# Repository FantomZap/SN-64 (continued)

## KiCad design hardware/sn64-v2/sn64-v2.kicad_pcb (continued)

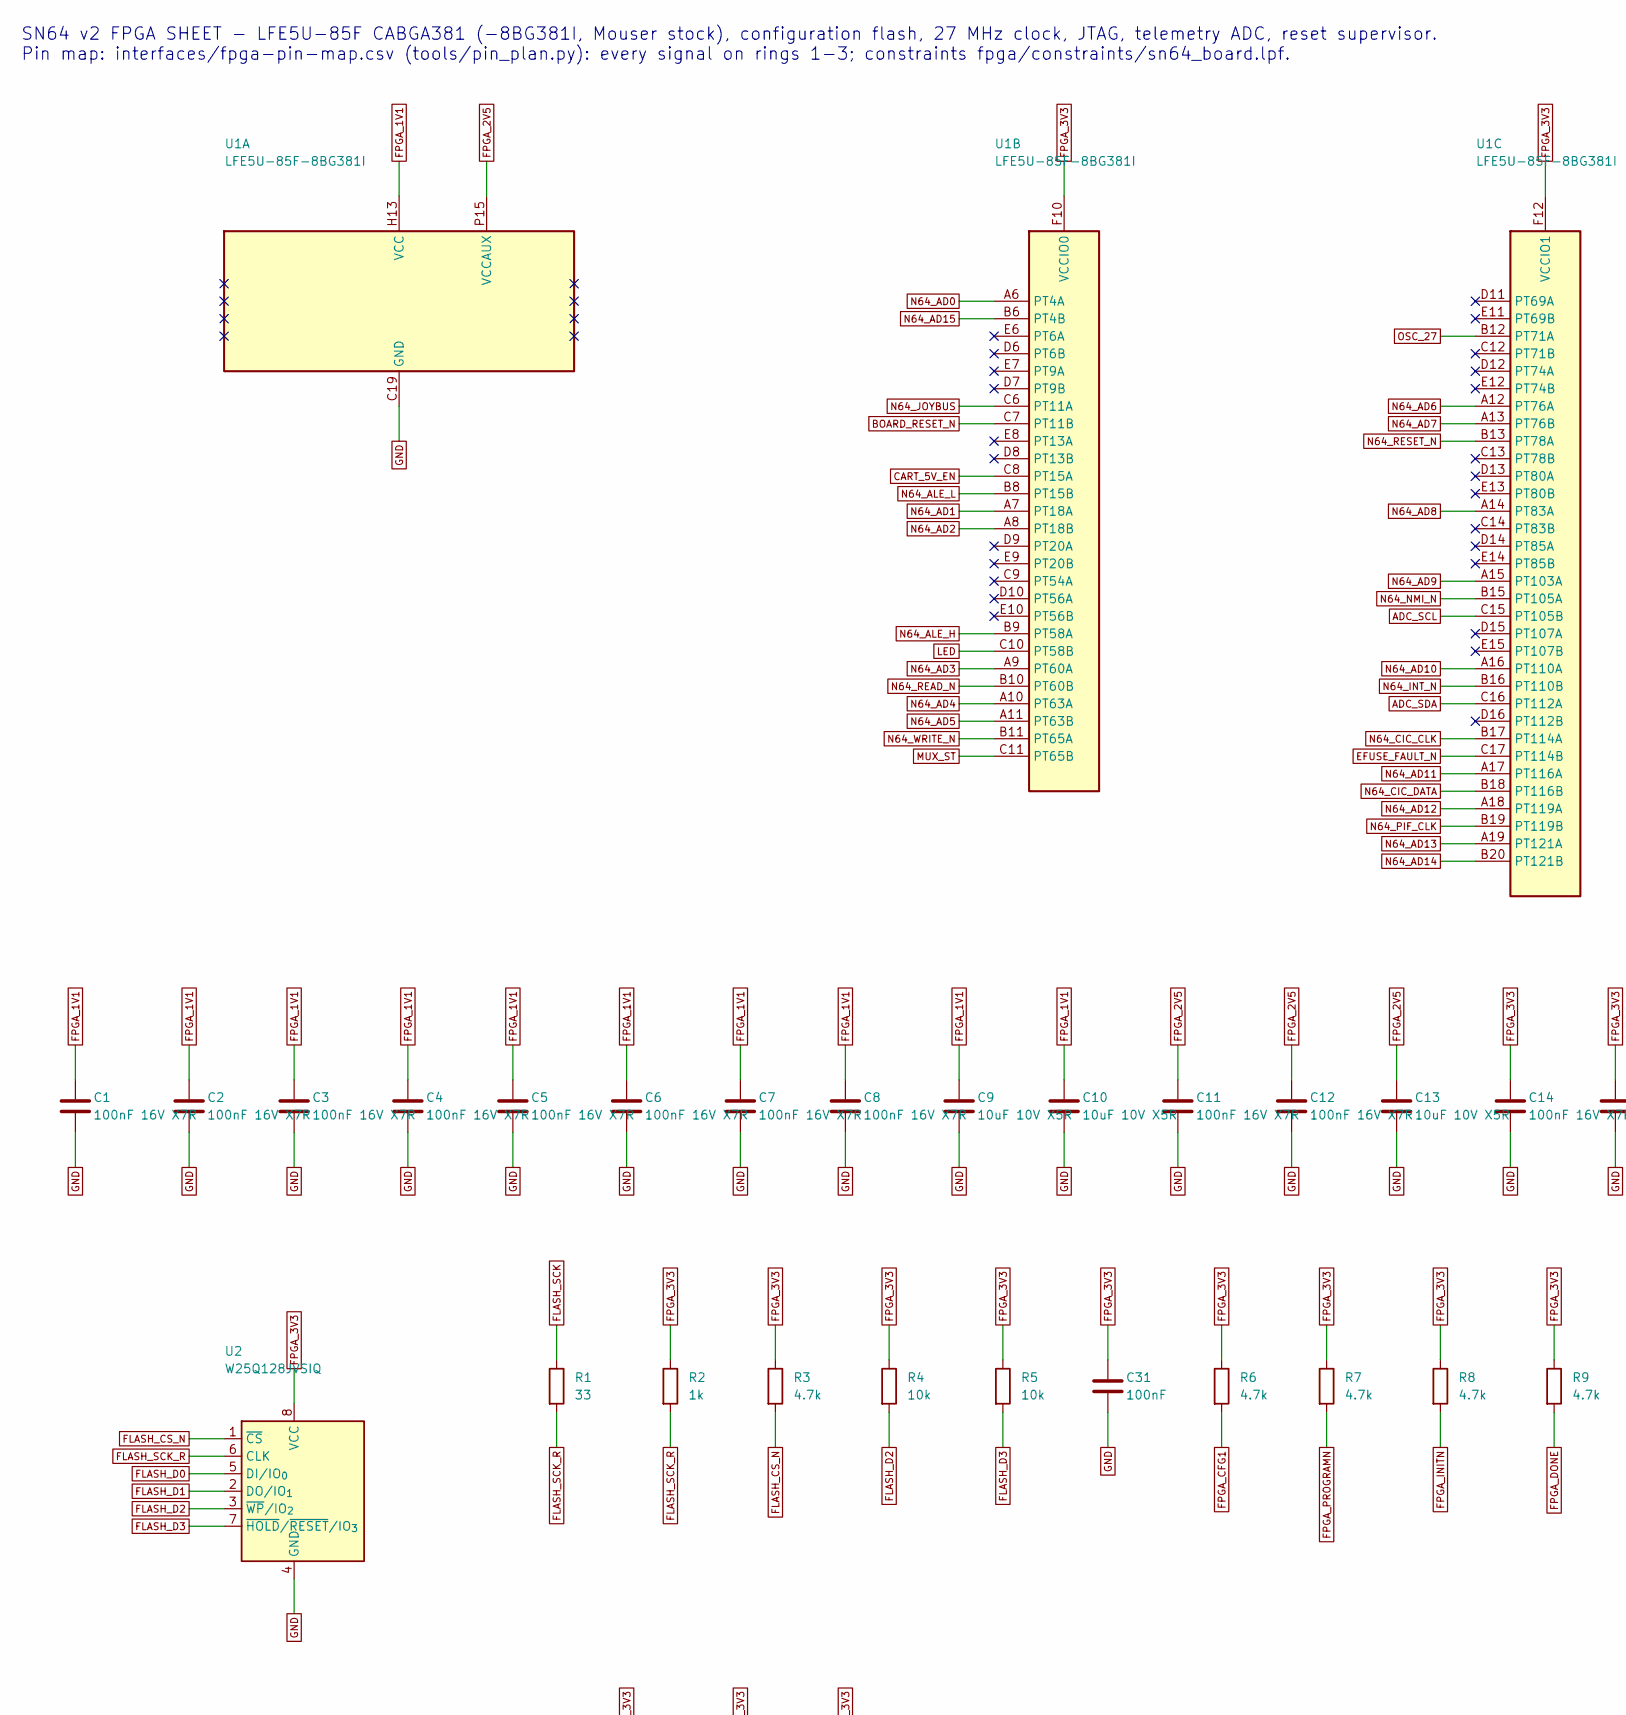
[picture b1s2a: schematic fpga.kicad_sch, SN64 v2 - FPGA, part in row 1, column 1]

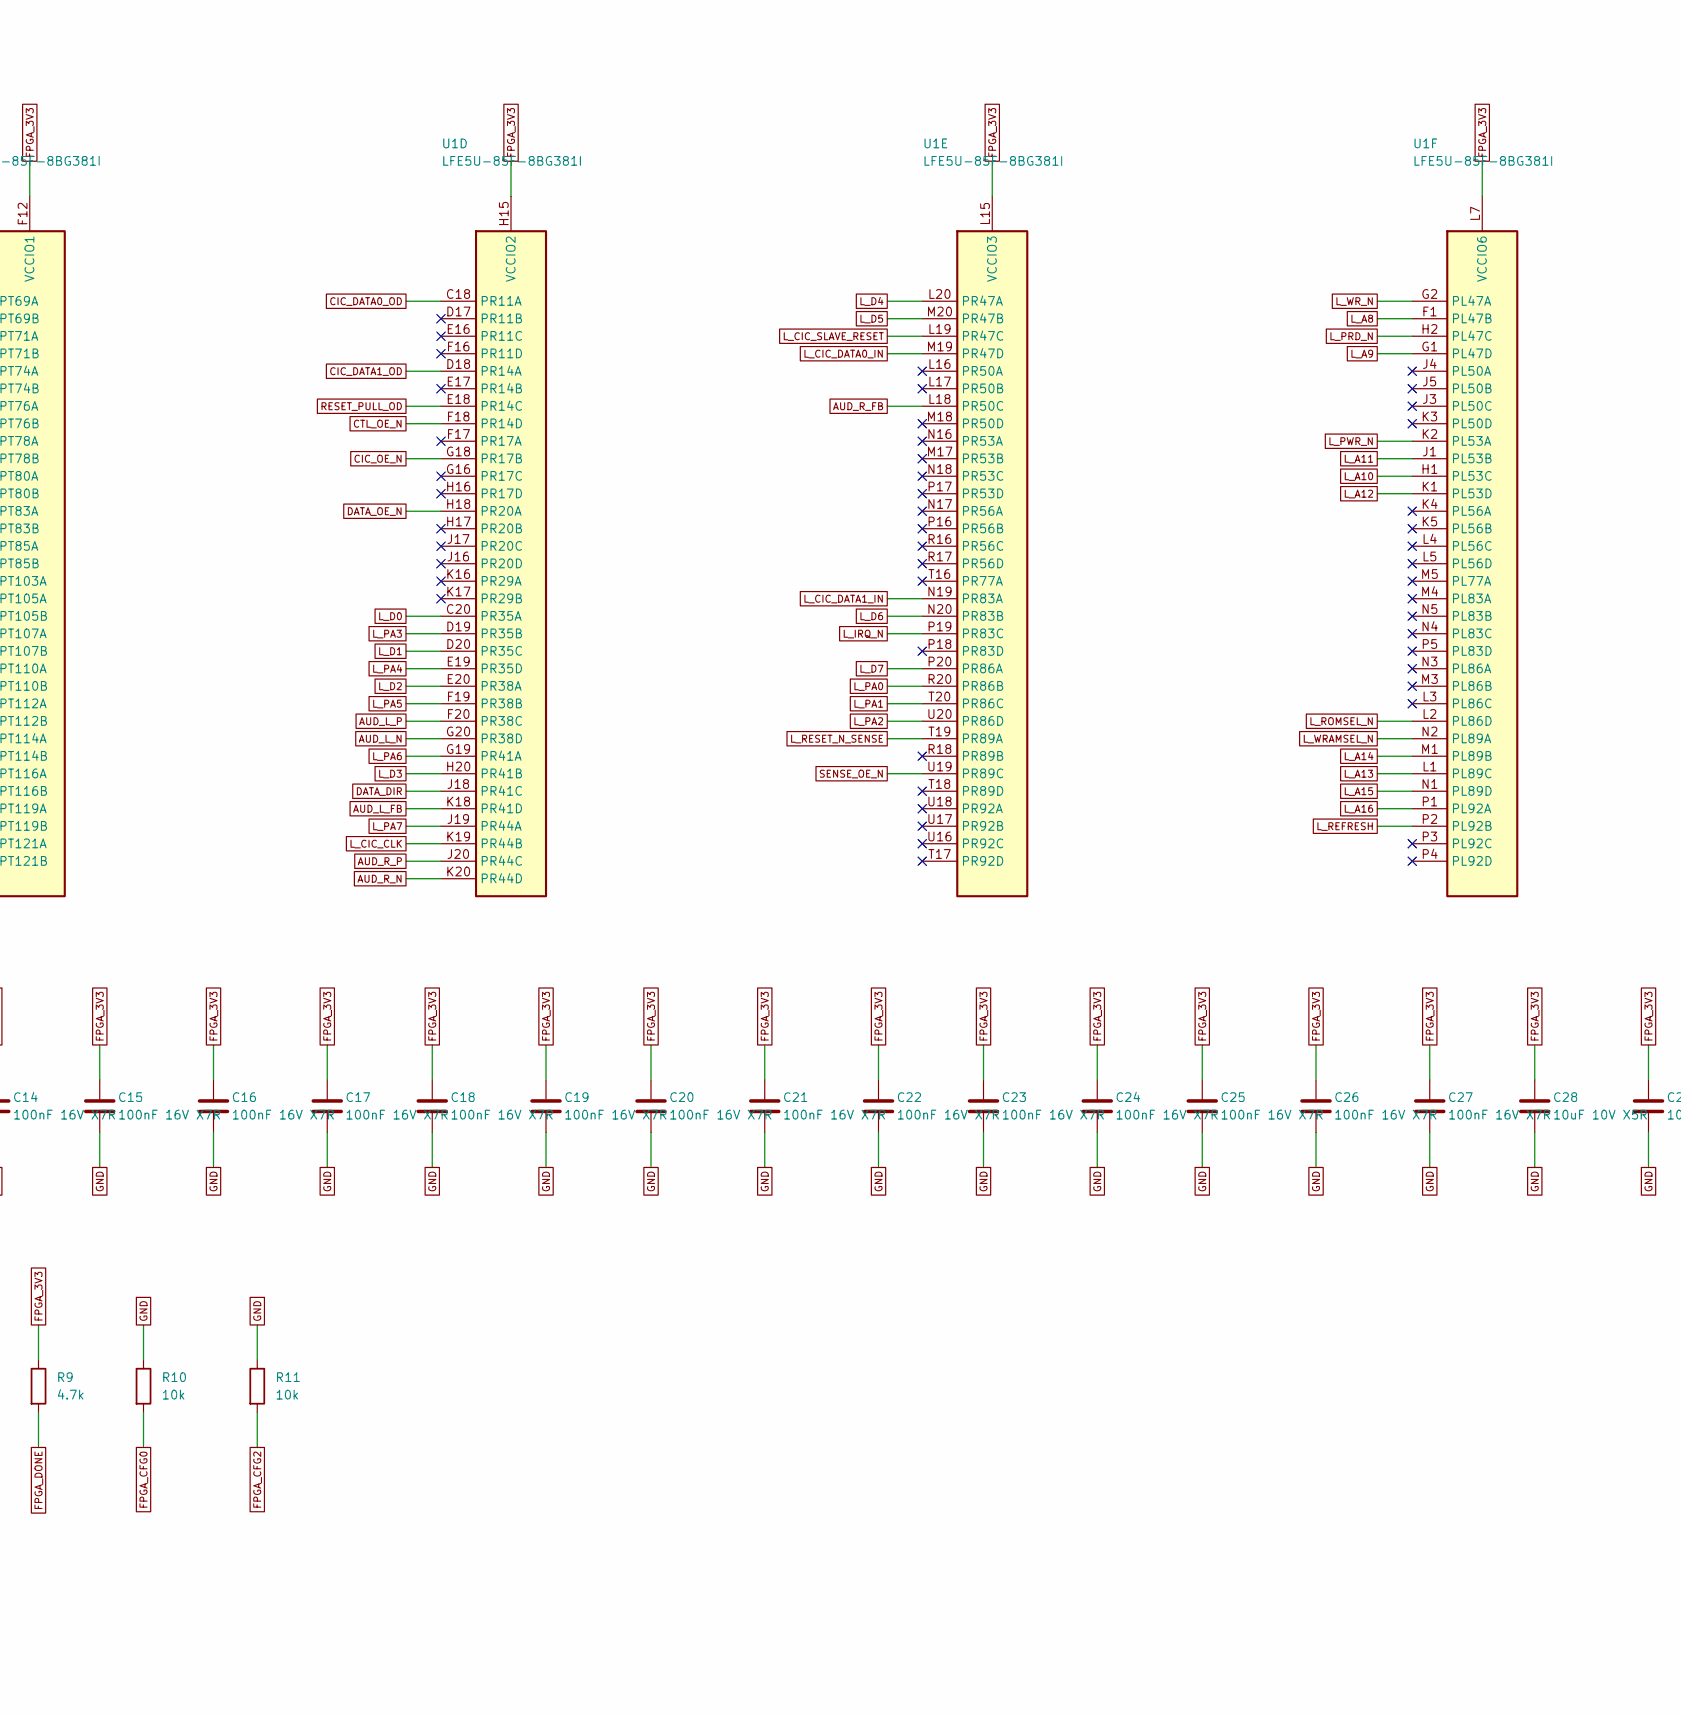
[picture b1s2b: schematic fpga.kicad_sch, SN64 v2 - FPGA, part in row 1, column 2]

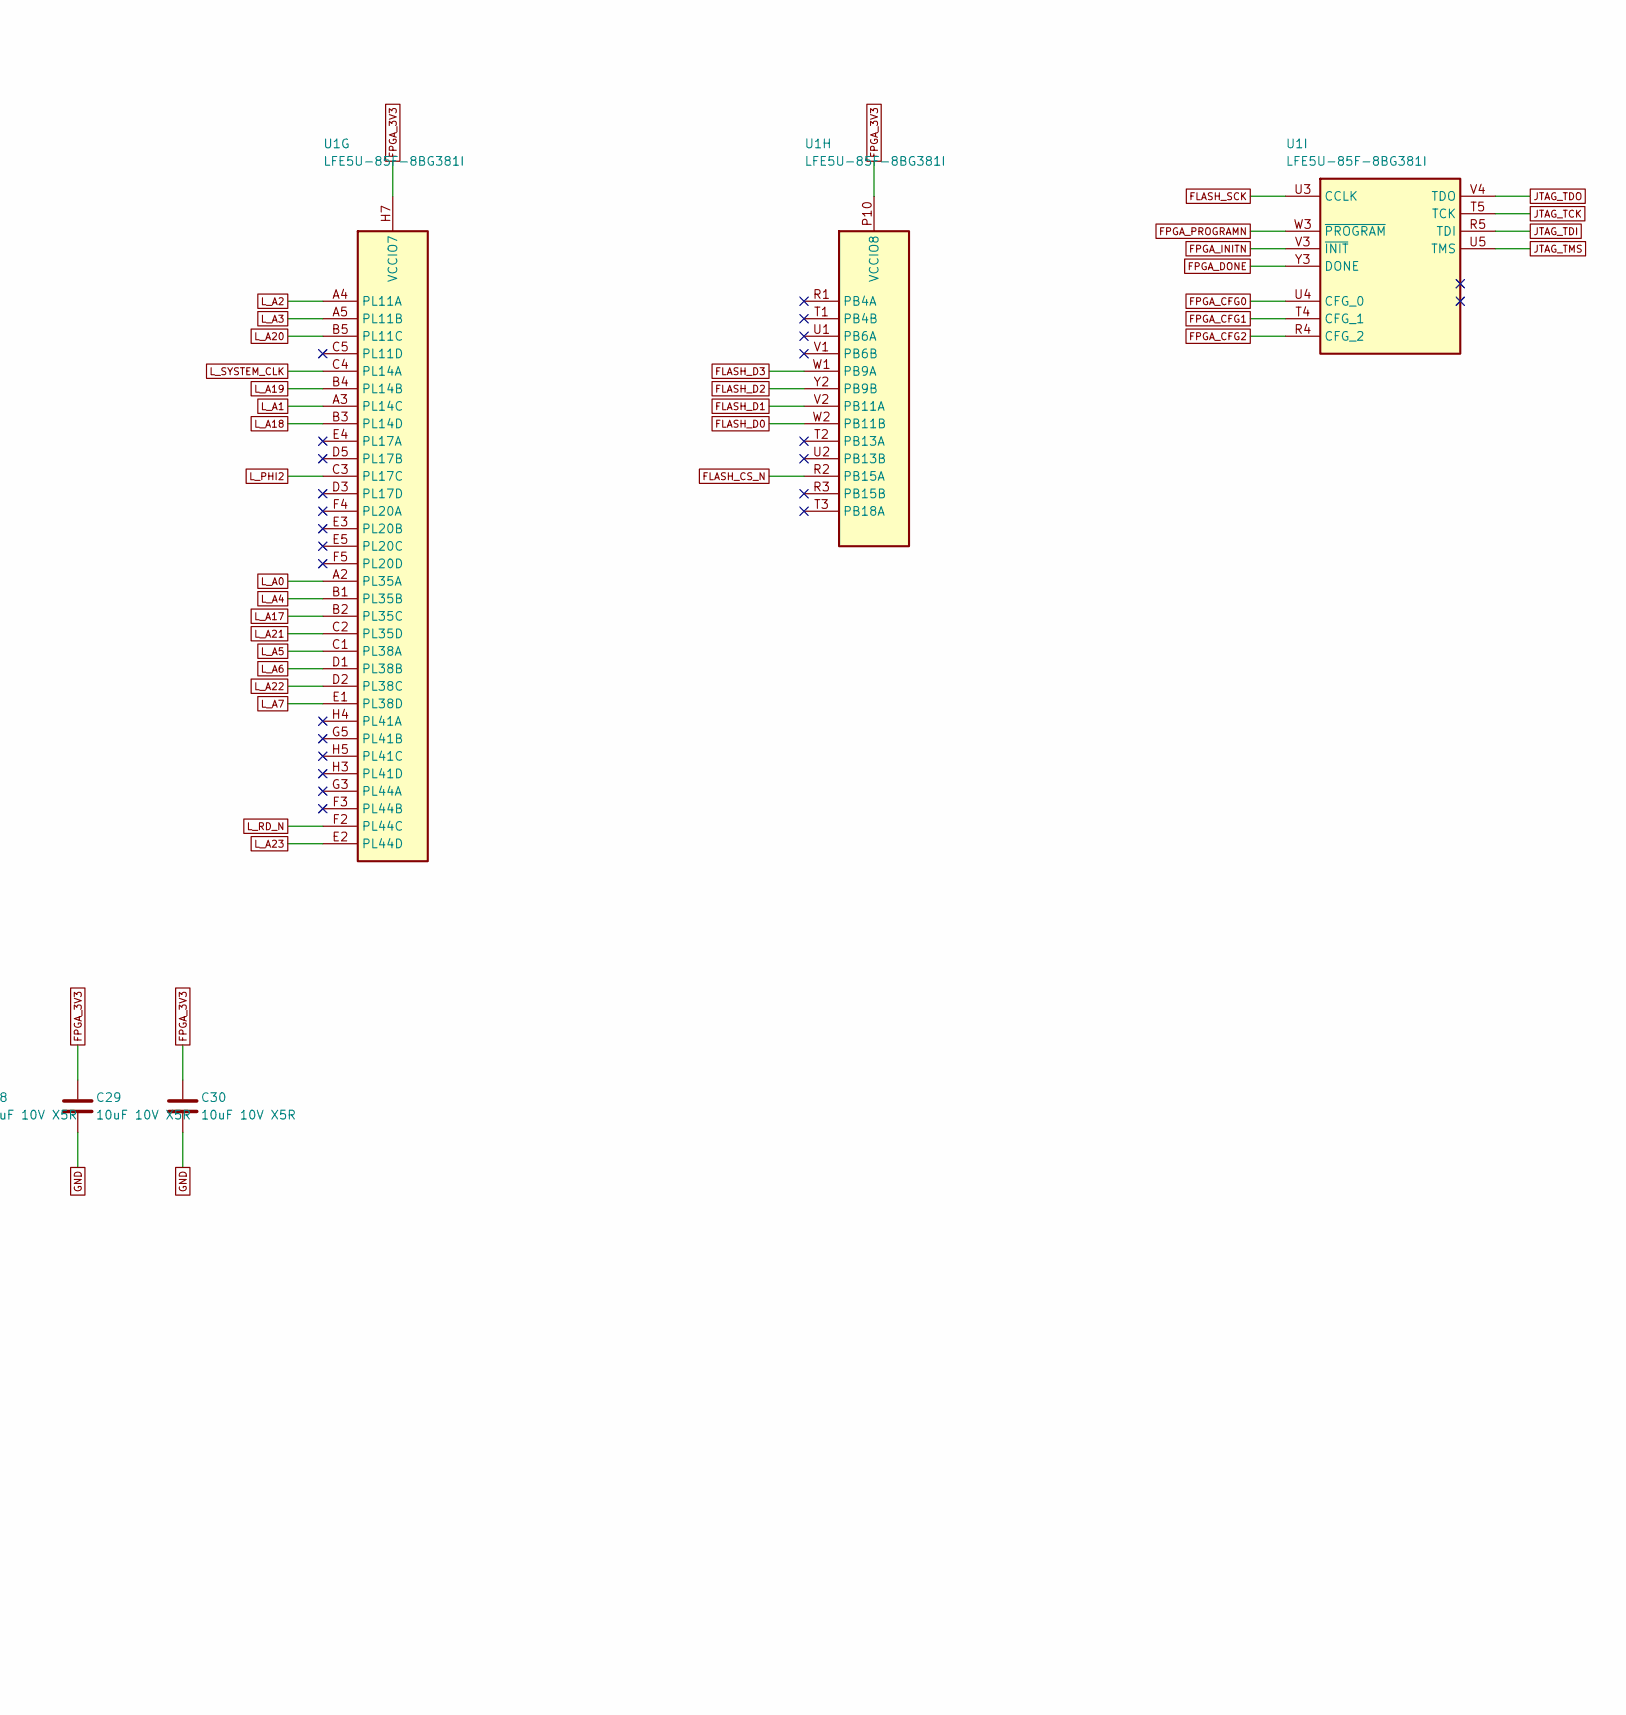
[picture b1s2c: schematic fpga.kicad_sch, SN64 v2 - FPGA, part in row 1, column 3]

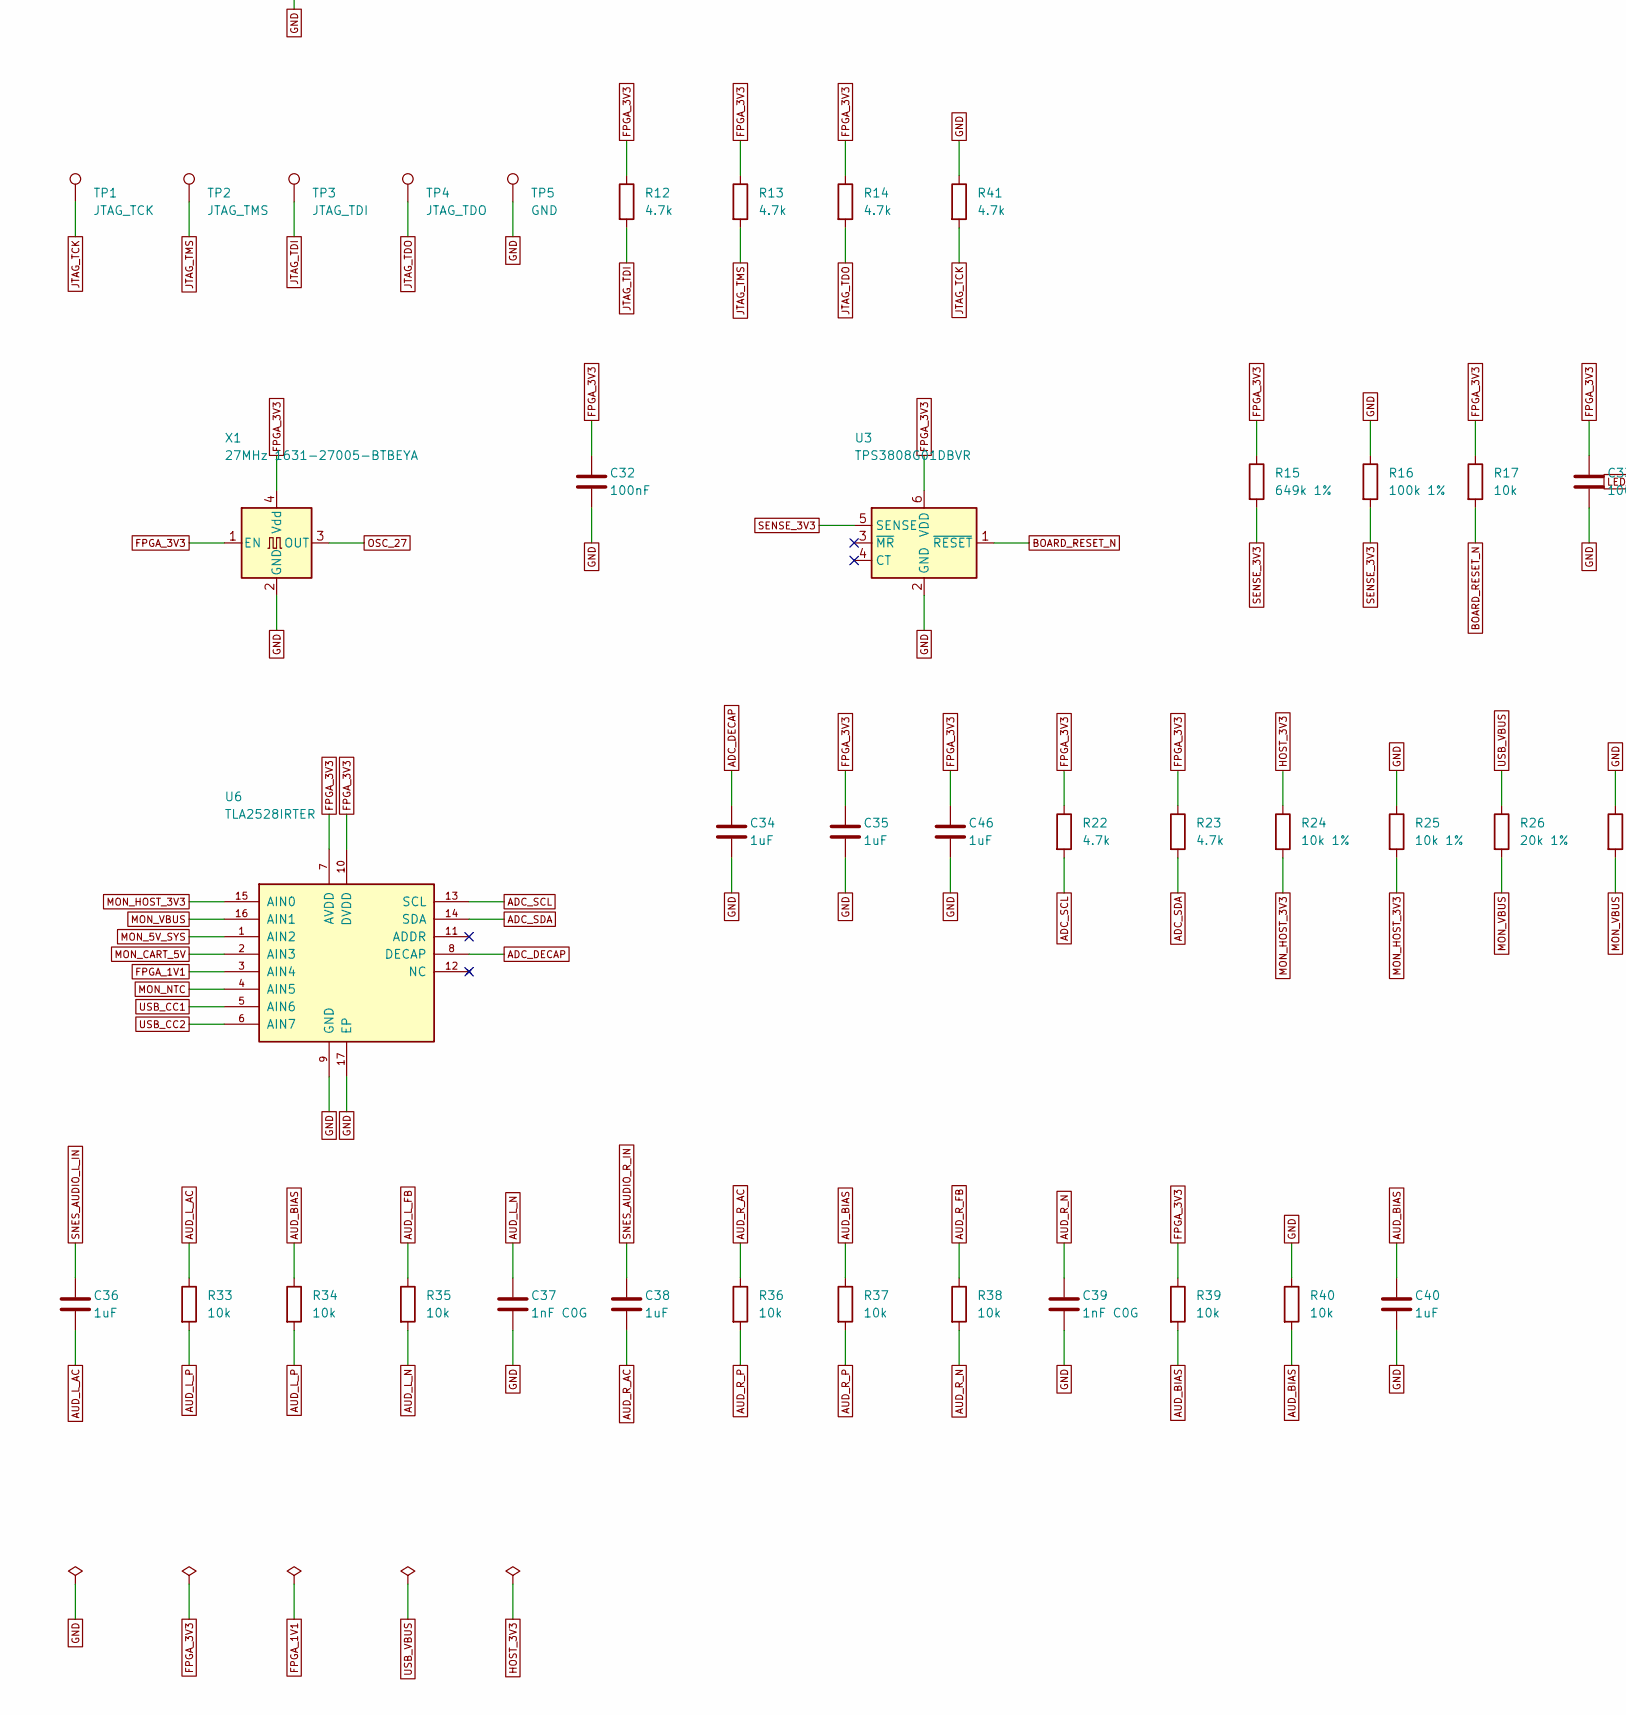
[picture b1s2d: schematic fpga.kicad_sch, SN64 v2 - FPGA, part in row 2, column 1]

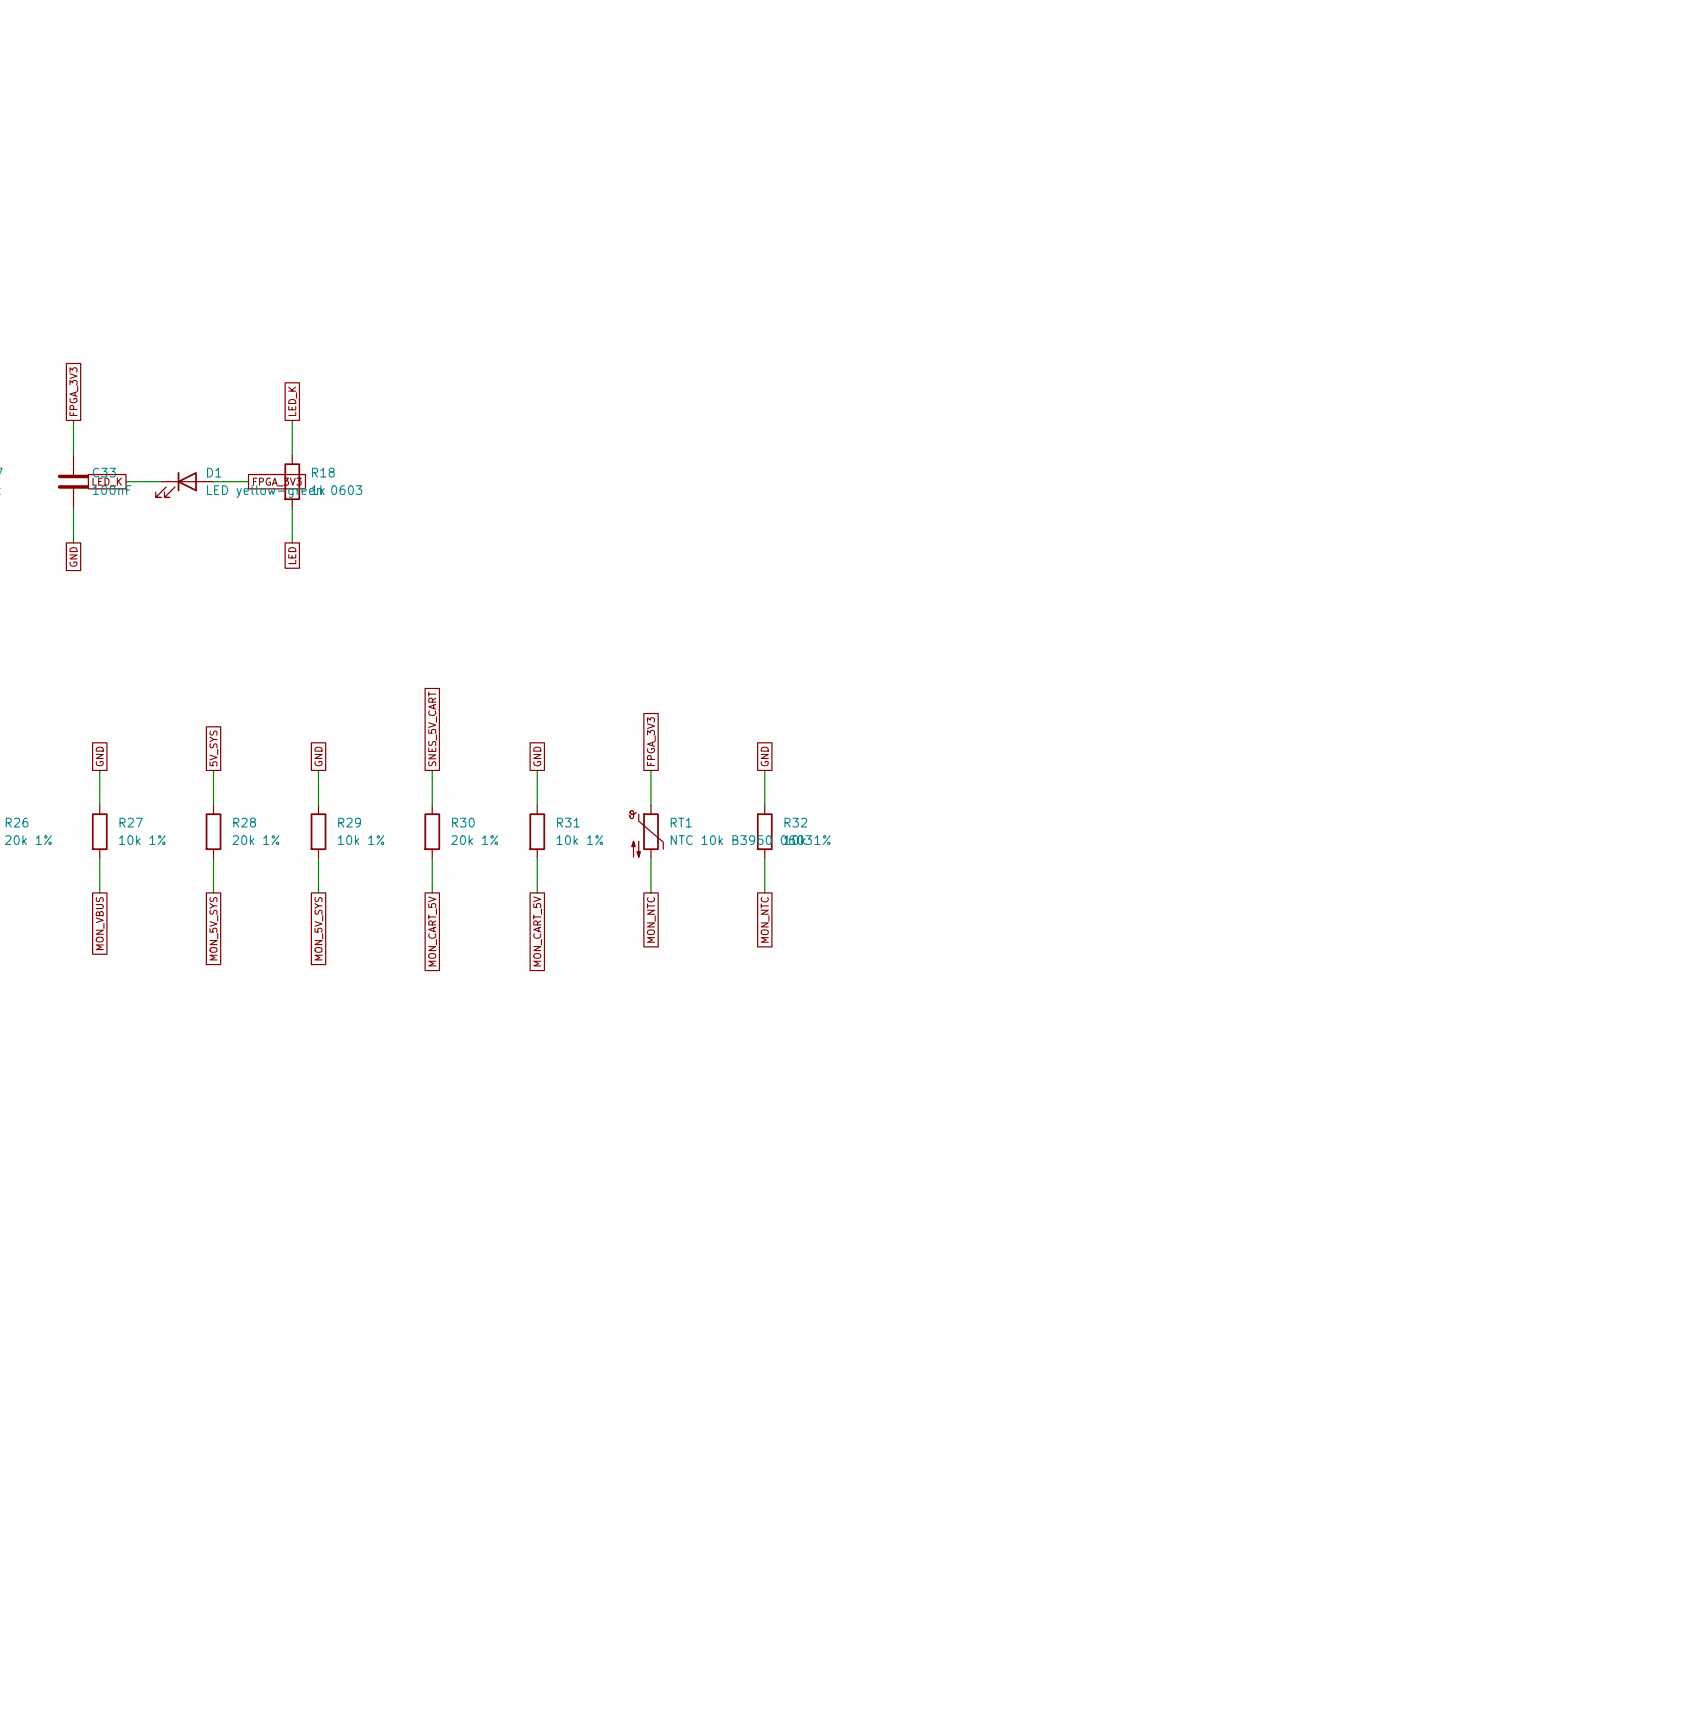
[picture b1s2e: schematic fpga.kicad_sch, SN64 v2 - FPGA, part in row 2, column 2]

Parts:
C1, C2, C3, C4, C5, C6, C7, C8, C11, C12, C14, C15, C16, C17, C18, C19, C20, C21, C22, C23, C24, C25, C26, C27: 100nF 16V X7R; C_0603_1608Metric; MPN CC0603KRX7R9BB104; LCSC C14663
C9, C10, C13, C28, C29, C30: 10uF 10V X5R; C_0805_2012Metric; MPN CL21A106KAYNNNE; LCSC C15850
C31, C32, C33: 100nF; C_0603_1608Metric; MPN CC0603KRX7R9BB104; LCSC C14663
C34, C35, C36, C38, C40, C46: 1uF; C_0603_1608Metric; MPN CL10A105KB8NNNC; LCSC C15849
C37, C39: 1nF C0G; C_0603_1608Metric; MPN CL10C102JB8NNNC; LCSC C163508
D1: LED yellow-green 0603; LED_0603_1608Metric; MPN 19-21SYGC/S530-E2/4T; LCSC C2986011
R1: 33; R_0603_1608Metric; MPN 0603WAF330JT5E; LCSC C23140
R2, R18: 1k; R_0603_1608Metric; MPN 0603WAF1001T5E; LCSC C21190
R3, R6, R7, R8, R9, R12, R13, R14, R22, R23, R41: 4.7k; R_0603_1608Metric; MPN 0603WAF4701T5E; LCSC C23162
R4, R5, R10, R11, R17, R33, R34, R35, R36, R37, R38, R39, R40: 10k; R_0603_1608Metric; MPN 0603WAF1002T5E; LCSC C25804
R15: 649k 1%; R_0603_1608Metric; MPN FRC0603F6493TS; LCSC C2999594
R16: 100k 1%; R_0603_1608Metric; MPN 0603WAF1003T5E; LCSC C25803
R24, R25, R27, R29, R31, R32: 10k 1%; R_0603_1608Metric; MPN 0603WAF1002T5E; LCSC C25804
R26, R28, R30: 20k 1%; R_0603_1608Metric; MPN 0603WAF2002T5E; LCSC C4184
RT1: NTC 10k B3950 0603; R_0603_1608Metric; MPN SDNT1608X103F3950FTF; LCSC C279936
TP1: JTAG_TCK; TestPoint_Pad_1.5x1.5mm
TP2: JTAG_TMS; TestPoint_Pad_1.5x1.5mm
TP3: JTAG_TDI; TestPoint_Pad_1.5x1.5mm
TP4: JTAG_TDO; TestPoint_Pad_1.5x1.5mm
TP5: GND; TestPoint_Pad_1.5x1.5mm
U1: LFE5U-85F-8BG381I; Lattice_caBGA-381_17x17mm_Layout20x20_P0.8mm; MPN LFE5U-85F-8BG381I
U2: W25Q128JVSIQ; SOIC-8_5.3x5.3mm_P1.27mm; MPN W25Q128JVSIQ; LCSC C97521
U3: TPS3808G01DBVR; SOT-23-6; MPN TPS3808G01DBVR; LCSC C19653
U6: TLA2528IRTER; WQFN-16-1EP_3x3mm_P0.5mm_EP1.68x1.68mm; MPN TLA2528IRTER; LCSC C2866175
X1: 27MHz 1631-27005-BTBEYA; Oscillator_SMD_Abracon_ASE-4Pin_3.2x2.5mm; MPN 1631-27005-BTBEYA; LCSC C3003262

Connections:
5V_SYS: R28.1; also elsewhere on the board
ADC_DECAP: C34.1, U6.8 (DECAP)
ADC_SCL: R22.2, U1.C15 (PT105B), U6.13 (SCL)
ADC_SDA: R23.2, U1.C16 (PT112A), U6.14 (SDA)
AUD_BIAS: C40.1, R34.1, R37.1, R39.2, R40.2
AUD_L_AC: C36.2, R33.1
AUD_L_FB: R35.1, U1.K18 (PR41D)
AUD_L_N: C37.1, R35.2, U1.G20 (PR38D)
AUD_L_P: R33.2, R34.2, U1.F20 (PR38C)
AUD_R_AC: C38.2, R36.1
AUD_R_FB: R38.1, U1.L18 (PR50C)
AUD_R_N: C39.1, R38.2, U1.K20 (PR44D)
AUD_R_P: R36.2, R37.2, U1.J20 (PR44C)
BOARD_RESET_N: R17.2, U1.C7 (PT11B), U3.1 (~RESET)
CART_5V_EN: U1.C8 (PT15A); also elsewhere on the board
CIC_DATA0_OD: U1.C18 (PR11A); also elsewhere on the board
CIC_DATA1_OD: U1.D18 (PR14A); also elsewhere on the board
CIC_OE_N: U1.G18 (PR17B); also elsewhere on the board
CTL_OE_N: U1.F18 (PR14D); also elsewhere on the board
DATA_DIR: U1.J18 (PR41C); also elsewhere on the board
DATA_OE_N: U1.H18 (PR20A); also elsewhere on the board
EFUSE_FAULT_N: U1.C17 (PT114B); also elsewhere on the board
FLASH_CS_N: R3.2, U1.R2 (PB15A), U2.1 (~CS)
FLASH_D0: U1.W2 (PB11B), U2.5 (DI/IO_{0})
FLASH_D1: U1.V2 (PB11A), U2.2 (DO/IO_{1})
FLASH_D2: R4.2, U1.Y2 (PB9B), U2.3 (~WP/IO_{2})
FLASH_D3: R5.2, U1.W1 (PB9A), U2.7 (~HOLD/~RESET/IO_{3})
FLASH_SCK: R1.1, U1.U3 (CCLK)
FLASH_SCK_R: R1.2, R2.2, U2.6 (CLK)
FPGA_1V1: C1.1, C2.1, C3.1, C4.1, C5.1, C6.1, C7.1, C8.1, C9.1, C10.1, U1.H8 (VCC), U1.H9 (VCC), U1.H10 (VCC), U1.H11 (VCC), U1.H12 (VCC), U1.H13 (VCC), U1.J8 (VCC), U1.J13 (VCC), U1.K8 (VCC), U1.K13 (VCC), U1.L8 (VCC), U1.L13 (VCC), U1.M8 (VCC), U1.M13 (VCC), U1.N8 (VCC), U1.N9 (VCC), U1.N10 (VCC), U1.N11 (VCC), U1.N12 (VCC), U1.N13 (VCC), U6.3 (AIN4); also elsewhere on the board
FPGA_2V5: C11.1, C12.1, C13.1, U1.F6 (VCCAUX), U1.F15 (VCCAUX), U1.P6 (VCCAUX), U1.P15 (VCCAUX); also elsewhere on the board
FPGA_3V3: C14.1, C15.1, C16.1, C17.1, C18.1, C19.1, C20.1, C21.1, C22.1, C23.1, C24.1, C25.1, C26.1, C27.1, C28.1, C29.1, C30.1, C31.1, C32.1, C33.1, C35.1, C46.1, D1.2 (A), R2.1, R3.1, R4.1, R5.1, R6.1, R7.1, R8.1, R9.1, R12.1, R13.1, R14.1, R15.1, R17.1, R22.1, R23.1, R39.1, RT1.1, U1.F9 (VCCIO0), U1.F10 (VCCIO0), U1.F11 (VCCIO1), U1.F12 (VCCIO1), U1.H6 (VCCIO7), U1.H7 (VCCIO7), U1.H14 (VCCIO2), U1.H15 (VCCIO2), U1.J6 (VCCIO7), U1.J15 (VCCIO2), U1.L6 (VCCIO6), U1.L7 (VCCIO6), U1.L14 (VCCIO3), U1.L15 (VCCIO3), U1.M6 (VCCIO6), U1.M15 (VCCIO3), U1.P9 (VCCIO8), U1.P10 (VCCIO8), U2.8 (VCC), U3.6 (VDD), U6.7 (AVDD), U6.10 (DVDD), X1.1 (EN), X1.4 (Vdd); also elsewhere on the board
FPGA_CFG0: R10.2, U1.U4 (CFG_0)
FPGA_CFG1: R6.2, U1.T4 (CFG_1)
FPGA_CFG2: R11.2, U1.R4 (CFG_2)
FPGA_DONE: R9.2, U1.Y3 (DONE)
FPGA_INITN: R8.2, U1.V3 (~INIT)
FPGA_PROGRAMN: R7.2, U1.W3 (~PROGRAM)
GND: C1.2, C2.2, C3.2, C4.2, C5.2, C6.2, C7.2, C8.2, C9.2, C10.2, C11.2, C12.2, C13.2, C14.2, C15.2, C16.2, C17.2, C18.2, C19.2, C20.2, C21.2, C22.2, C23.2, C24.2, C25.2, C26.2, C27.2, C28.2, C29.2, C30.2, C31.2, C32.2, C33.2, C34.2, C35.2, C37.2, C39.2, C40.2, C46.2, R10.1, R11.1, R16.1, R25.1, R27.1, R29.1, R31.1, R32.1, R40.1, R41.1, TP5.1, U1.B7 (GND), U1.B14 (GND), U1.C19 (GND), U1.D4 (GND), U1.F7 (GND), U1.F8 (GND), U1.F13 (GND), U1.F14 (GND), U1.G4 (GND), U1.G6 (GND), U1.G7 (GND), U1.G8 (GND), U1.G9 (GND), U1.G10 (GND), U1.G11 (GND), U1.G12 (GND), U1.G13 (GND), U1.G14 (GND), U1.G15 (GND), U1.G17 (GND), U1.H19 (GND), U1.J2 (GND), U1.J7 (GND), U1.J9 (GND), U1.J10 (GND), U1.J11 (GND), U1.J12 (GND), U1.J14 (GND), U1.K6 (GND), U1.K7 (GND), U1.K9 (GND), U1.K10 (GND), U1.K11 (GND), U1.K12 (GND), U1.K14 (GND), U1.K15 (GND), U1.L9 (GND), U1.L10 (GND), U1.L11 (GND), U1.L12 (GND), U1.M2 (GND), U1.M7 (GND), U1.M9 (GND), U1.M10 (GND), U1.M11 (GND), U1.M12 (GND), U1.M14 (GND), U1.M16 (GND), U1.N6 (GND), U1.N7 (GND), U1.N14 (GND), U1.N15 (GND), U1.P7 (GND), U1.P8 (GND), U1.P11 (GND), U1.P12 (GND), U1.P13 (GND), U1.P14 (GND), U1.R19 (GND), U1.T6 (GND), U1.T7 (GND), U1.T8 (GND), U1.T9 (GND), U1.T10 (GND), U1.T11 (GND), U1.T12 (GND), U1.T13 (GND), U1.T14 (GND), U1.T15 (GND), U1.U6 (GND), U1.U7 (GND), U1.U8 (GND), U1.U9 (GND), U1.U10 (GND), U1.U11 (GND), U1.U12 (GND), U1.U13 (GND), U1.U14 (GND), U1.U15 (GND), U1.V5 (GND), U1.V6 (GND), U1.V7 (GND), U1.V8 (GND), U1.V9 (GND), U1.V10 (GND), U1.V11 (GND), U1.V12 (GND), U1.V13 (GND), U1.V14 (GND), U1.V15 (GND), U1.V16 (GND), U1.V17 (GND), U1.V18 (GND), U1.V19 (GND), U1.V20 (GND), U1.W6 (GND), U1.W7 (GND), U1.W12 (GND), U1.W15 (GND), U1.W16 (GND), U1.W19 (GND), U1.W20 (GND), U1.Y5 (GND), U1.Y6 (GND), U1.Y7 (GND), U1.Y8 (GND), U1.Y11 (GND), U1.Y12 (GND), U1.Y14 (GND), U1.Y15 (GND), U1.Y16 (GND), U1.Y17 (GND), U1.Y19 (GND), U2.4 (GND), U3.2 (GND), U6.9 (GND), U6.17 (EP), X1.2 (GND); also elsewhere on the board
HOST_3V3: R24.1; also elsewhere on the board
JTAG_TCK: R41.2, TP1.1, U1.T5 (TCK); also elsewhere on the board
JTAG_TDI: R12.2, TP3.1, U1.R5 (TDI); also elsewhere on the board
JTAG_TDO: R14.2, TP4.1, U1.V4 (TDO); also elsewhere on the board
JTAG_TMS: R13.2, TP2.1, U1.U5 (TMS); also elsewhere on the board
LED: R18.2, U1.C10 (PT58B)
LED_K: D1.1 (K), R18.1
L_A0: U1.A2 (PL35A); also elsewhere on the board
L_A1: U1.A3 (PL14C); also elsewhere on the board
L_A2: U1.A4 (PL11A); also elsewhere on the board
L_A3: U1.A5 (PL11B); also elsewhere on the board
L_A4: U1.B1 (PL35B); also elsewhere on the board
L_A5: U1.C1 (PL38A); also elsewhere on the board
L_A6: U1.D1 (PL38B); also elsewhere on the board
L_A7: U1.E1 (PL38D); also elsewhere on the board
L_A8: U1.F1 (PL47B); also elsewhere on the board
L_A9: U1.G1 (PL47D); also elsewhere on the board
L_A10: U1.H1 (PL53C); also elsewhere on the board
L_A11: U1.J1 (PL53B); also elsewhere on the board
L_A12: U1.K1 (PL53D); also elsewhere on the board
L_A13: U1.L1 (PL89C); also elsewhere on the board
L_A14: U1.M1 (PL89B); also elsewhere on the board
L_A15: U1.N1 (PL89D); also elsewhere on the board
L_A16: U1.P1 (PL92A); also elsewhere on the board
L_A17: U1.B2 (PL35C); also elsewhere on the board
L_A18: U1.B3 (PL14D); also elsewhere on the board
L_A19: U1.B4 (PL14B); also elsewhere on the board
L_A20: U1.B5 (PL11C); also elsewhere on the board
L_A21: U1.C2 (PL35D); also elsewhere on the board
L_A22: U1.D2 (PL38C); also elsewhere on the board
L_A23: U1.E2 (PL44D); also elsewhere on the board
L_CIC_CLK: U1.K19 (PR44B); also elsewhere on the board
L_CIC_DATA0_IN: U1.M19 (PR47D); also elsewhere on the board
L_CIC_DATA1_IN: U1.N19 (PR83A); also elsewhere on the board
L_CIC_SLAVE_RESET: U1.L19 (PR47C); also elsewhere on the board
L_D0: U1.C20 (PR35A); also elsewhere on the board
L_D1: U1.D20 (PR35C); also elsewhere on the board
L_D2: U1.E20 (PR38A); also elsewhere on the board
L_D3: U1.H20 (PR41B); also elsewhere on the board
L_D4: U1.L20 (PR47A); also elsewhere on the board
L_D5: U1.M20 (PR47B); also elsewhere on the board
L_D6: U1.N20 (PR83B); also elsewhere on the board
L_D7: U1.P20 (PR86A); also elsewhere on the board
L_IRQ_N: U1.P19 (PR83C); also elsewhere on the board
L_PA0: U1.R20 (PR86B); also elsewhere on the board
L_PA1: U1.T20 (PR86C); also elsewhere on the board
L_PA2: U1.U20 (PR86D); also elsewhere on the board
L_PA3: U1.D19 (PR35B); also elsewhere on the board
L_PA4: U1.E19 (PR35D); also elsewhere on the board
L_PA5: U1.F19 (PR38B); also elsewhere on the board
L_PA6: U1.G19 (PR41A); also elsewhere on the board
L_PA7: U1.J19 (PR44A); also elsewhere on the board
L_PHI2: U1.C3 (PL17C); also elsewhere on the board
L_PRD_N: U1.H2 (PL47C); also elsewhere on the board
L_PWR_N: U1.K2 (PL53A); also elsewhere on the board
L_RD_N: U1.F2 (PL44C); also elsewhere on the board
L_REFRESH: U1.P2 (PL92B); also elsewhere on the board
L_RESET_N_SENSE: U1.T19 (PR89A); also elsewhere on the board
L_ROMSEL_N: U1.L2 (PL86D); also elsewhere on the board
L_SYSTEM_CLK: U1.C4 (PL14A); also elsewhere on the board
L_WRAMSEL_N: U1.N2 (PL89A); also elsewhere on the board
L_WR_N: U1.G2 (PL47A); also elsewhere on the board
MON_5V_SYS: R28.2, R29.2, U6.1 (AIN2)
MON_CART_5V: R30.2, R31.2, U6.2 (AIN3)
MON_HOST_3V3: R24.2, R25.2, U6.15 (AIN0)
MON_NTC: R32.2, RT1.2, U6.4 (AIN5)
MON_VBUS: R26.2, R27.2, U6.16 (AIN1)
MUX_ST: U1.C11 (PT65B); also elsewhere on the board
N64_AD0: U1.A6 (PT4A); also elsewhere on the board
N64_AD1: U1.A7 (PT18A); also elsewhere on the board
N64_AD2: U1.A8 (PT18B); also elsewhere on the board
N64_AD3: U1.A9 (PT60A); also elsewhere on the board
N64_AD4: U1.A10 (PT63A); also elsewhere on the board
N64_AD5: U1.A11 (PT63B); also elsewhere on the board
N64_AD6: U1.A12 (PT76A); also elsewhere on the board
N64_AD7: U1.A13 (PT76B); also elsewhere on the board
N64_AD8: U1.A14 (PT83A); also elsewhere on the board
N64_AD9: U1.A15 (PT103A); also elsewhere on the board
N64_AD10: U1.A16 (PT110A); also elsewhere on the board
N64_AD11: U1.A17 (PT116A); also elsewhere on the board
N64_AD12: U1.A18 (PT119A); also elsewhere on the board
N64_AD13: U1.A19 (PT121A); also elsewhere on the board
N64_AD14: U1.B20 (PT121B); also elsewhere on the board
N64_AD15: U1.B6 (PT4B); also elsewhere on the board
N64_ALE_H: U1.B9 (PT58A); also elsewhere on the board
N64_ALE_L: U1.B8 (PT15B); also elsewhere on the board
N64_CIC_CLK: U1.B17 (PT114A); also elsewhere on the board
N64_CIC_DATA: U1.B18 (PT116B); also elsewhere on the board
N64_INT_N: U1.B16 (PT110B); also elsewhere on the board
N64_JOYBUS: U1.C6 (PT11A); also elsewhere on the board
N64_NMI_N: U1.B15 (PT105A); also elsewhere on the board
N64_PIF_CLK: U1.B19 (PT119B); also elsewhere on the board
N64_READ_N: U1.B10 (PT60B); also elsewhere on the board
N64_RESET_N: U1.B13 (PT78A); also elsewhere on the board
N64_WRITE_N: U1.B11 (PT65A); also elsewhere on the board
OSC_27: U1.B12 (PT71A), X1.3 (OUT)
RESET_PULL_OD: U1.E18 (PR14C); also elsewhere on the board
SENSE_3V3: R15.2, R16.2, U3.5 (SENSE)
SENSE_OE_N: U1.U19 (PR89C); also elsewhere on the board
SNES_5V_CART: R30.1; also elsewhere on the board
SNES_AUDIO_L_IN: C36.1; also elsewhere on the board
SNES_AUDIO_R_IN: C38.1; also elsewhere on the board
USB_CC1: U6.5 (AIN6); also elsewhere on the board
USB_CC2: U6.6 (AIN7); also elsewhere on the board
USB_VBUS: R26.1; also elsewhere on the board

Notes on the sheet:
SN64 v2 FPGA SHEET - LFE5U-85F CABGA381 (-8BG381I, Mouser stock), configuration flash, 27 MHz clock, JTAG, telemetry ADC, reset supervisor. Pin map: interfaces/fpga-pin-map.csv (tools/pin_plan.py): every signal on rings 1-3; constraints fpga/constraints/sn64_board.lpf.
